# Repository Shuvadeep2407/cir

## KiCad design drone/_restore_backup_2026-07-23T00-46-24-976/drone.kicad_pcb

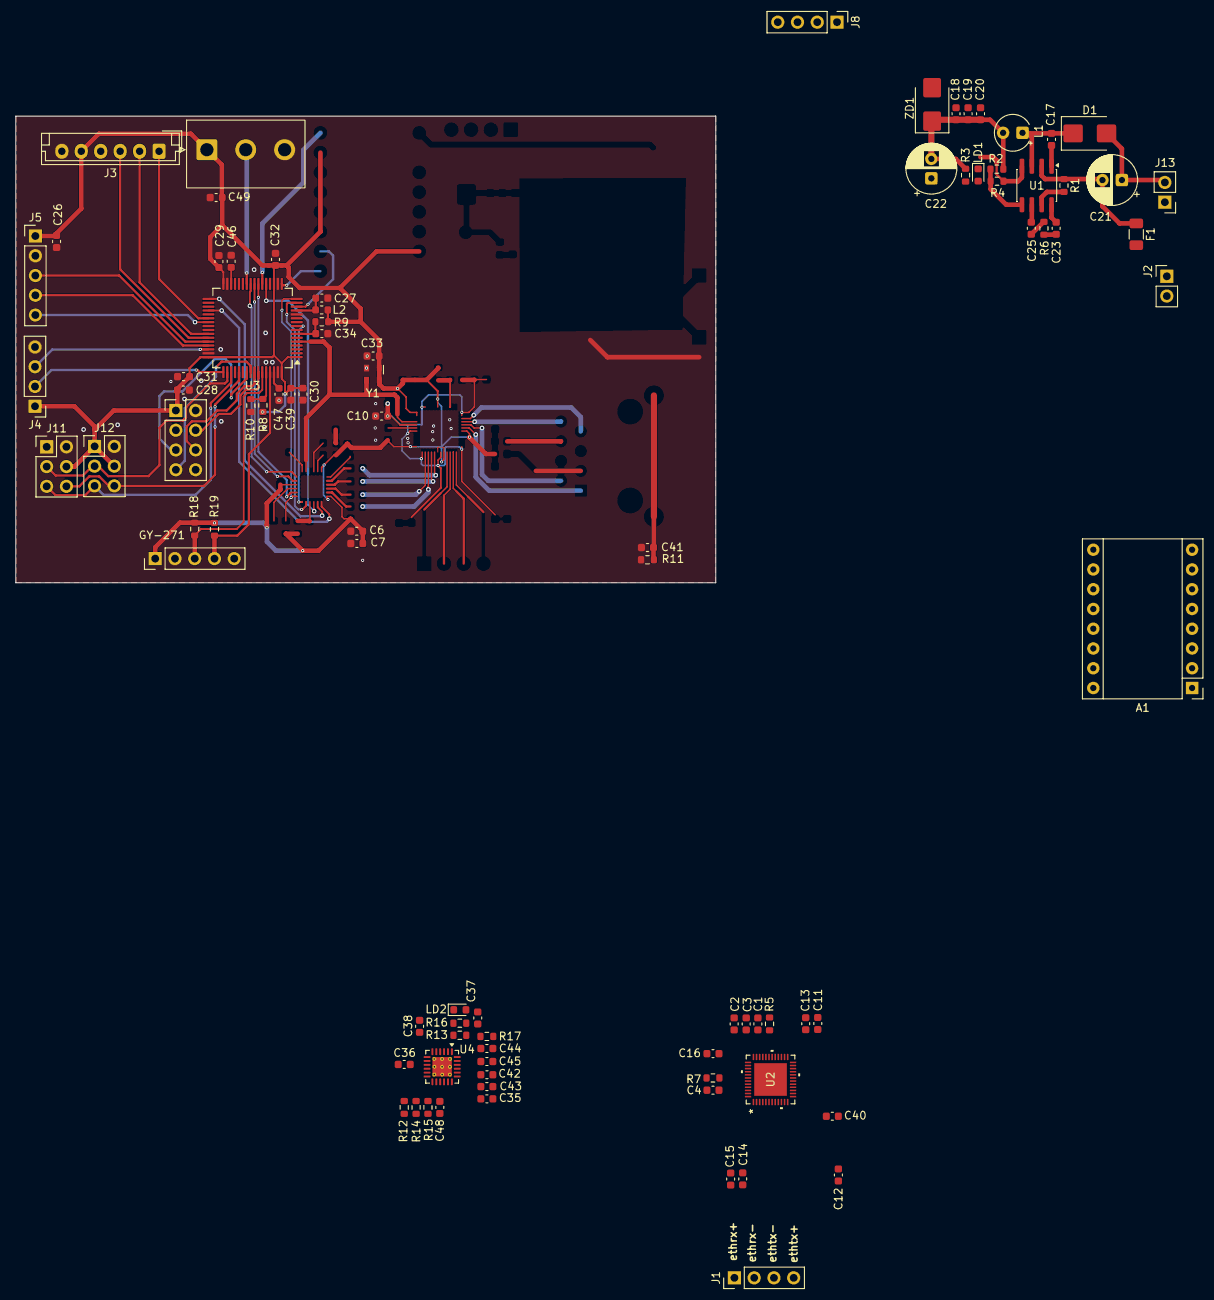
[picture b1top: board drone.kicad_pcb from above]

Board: 2 copper layers, 90.0 x 60.0 mm, 89 parts (0 on the bottom side), 75 nets.

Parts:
A1: A4988; Pololu_Breakout-16_15.2x20.3mm
C1, C2, C3, C4, C6, C7, C10, C11, C12, C13, C14, C15, C16, C17, C20, C23, C25, C26, C27, C28, C29, C30, C31, C32, C33, C34, C35, C36, C37, C38, C39, C40, C42, C43, C44, C45, C46, C47, C48, C49: 100nF; C_0603_1608Metric
C18: 10p; C_0603_1608Metric
C19: 33p; C_0603_1608Metric
C21, C22: 100uF D8.0mm_P3.50mm; CP_Radial_D6.3mm_P2.50mm
C41: 1nF; C_0603_1608Metric
D1: ss24; D_SMB
F1: 6w LIMIT; Fuse_1206_3216Metric
J1: cam eth; PinHeader_1x04_P2.54mm_Vertical
J2, J13: P_cam; PinHeader_1x02_P2.54mm_Vertical
J3: LRF; JST_EH_B6B-EH-A_1x06_P2.50mm_Vertical
J4: SWD; PinHeader_1x04_P2.54mm_Vertical
J5: gsm; PinHeader_1x05_P2.54mm_Vertical
J7: GY-271; PinHeader_1x05_P2.54mm_Vertical
J8: stapper; PinHeader_1x04_P2.54mm_Vertical
J9: C1101; PinHeader_2x04_P2.54mm_Vertical
J10: LIGHT; JST_NV_B03P-NV_1x03_P5.00mm_Vertical
J11, J12: INMP441; PinHeader_2x03_P2.54mm_Vertical
L1: 10µH; CP_Radial_Tantal_D4.5mm_P2.50mm
L2: 36nH; L_0603_1608Metric
LD1, LD2: LED; LED_0603_1608Metric
R1, R4, R5, R9, R10, R12, R13, R15, R18, R19: 10K; R_0603_1608Metric
R2: 26.1K; R_0603_1608Metric
R3, R16: 1K; R_0603_1608Metric
R6: 4k7; R_0603_1608Metric
R7: 2.49kΩ (1% tolerance); R_0603_1608Metric
R8: 100K; R_0603_1608Metric
R11: 1M; R_0603_1608Metric
R14: 4.7K; R_0603_1608Metric
R17: 12.1K; R_0603_1608Metric
U1: EUP3484A; SOIC-8_3.9x4.9mm_P1.27mm
U2: RTL8305NB-CG; QFN48_RTL8305_RTK
U3: STM32H563RGTx; LQFP-64_10x10mm_P0.5mm
U4: LAN8720A; VQFN-24-1EP_4x4mm_P0.5mm_EP2.5x2.5mm_ThermalVias
Y1: ASDMB-25MHz; Oscillator_SMD_Abracon_ASDMB-4Pin_2.5x2.0mm
ZD1: 3v3; D_SMB

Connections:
+3V3: A1.2 (VDD), A1.10 (MS1), A1.11 (MS2), A1.12 (MS3), A1.13 (~RESET), A1.14 (~SLEEP), C1.1, C2.1, C3.1, C4.1, C6.1, C7.1, C18.1, C19.1, C20.1, C22.2, C26.1, C28.1, C29.1, C30.1, C31.1, C32.1, C33.1, C35.1, C36.1, C37.1, C39.1, C40.1, C49.1, J3.5, J4.1, J5.1, J7.1, J9.1, J10.1, J11.4, J12.1, J12.4, L1.2, L2.1, R2.1, R3.1, R5.2, R8.2, R9.2, R13.1, R14.2, R15.2, R18.2, R19.2, U2.6 (AVDDH), U2.8 (AVDDH), U2.18 (AVDDH), U2.31 (DVDDH), U2.37 (V331N), U2.38 (AVDDHPLL), U2.48 (AVDDH), U3.1 (VBAT), U3.19 (VDD), U3.32 (VDD), U3.48 (VDD), U3.64 (VDD), U4.1 (VDD2A), U4.9 (VDDIO), U4.19 (VDD1A), Y1.1 (Standby), Y1.4 (VDD), ZD1.1 (K)
+12V: A1.8 (VMOT), C21.2, F1.1, J13.1, R1.1, U1.2 (IN)
/25MHz: U2.40 (XI), U3.5 (PH0), U4.5 (XTAL1/CLKIN), Y1.3 (Out)
/C1101 _clk: J9.5, U3.55 (PB3(JTDO)
/C1101 _cs: J9.4, U3.58 (PB6)
/C1101 _mosi: J9.6, U3.57 (PB5)
/C1101_miso: J9.7, U3.56 (PB4(NJTRST))
/CRS_DV: U3.23 (PA7), U4.11 (CRS_DV/MODE2)
/DIR: A1.16 (DIR), U3.17 (PA3)
/ENABLE: A1.9 (~ENABLE), U3.22 (PA6)
/LIGHT_EN: J10.2, U3.26 (PB0)
/LRF_EN: J3.1, U3.38 (PC7)
/LRF_RX: J3.2, U3.42 (PA9)
/LRF_TX: J3.3, U3.43 (PA10)
/MDC: U3.9 (PC1), U4.13 (MDC)
/MDIO: R14.1, U3.16 (PA2), U4.12 (MDIO)
/PPS: J5.5, U3.39 (PC8)
/REF_CLK: U3.15 (PA1), U4.14 (~INT/REFCLKO)
/RXD0: U3.24 (PC4), U4.8 (RXD0/MODE0)
/RXD1: U3.25 (PC5), U4.7 (RXD1/MODE1)
/STEP: A1.15 (STEP), U3.14 (PA0)
/SWCLK: J4.2, U3.49 (PA14(JTCK)
/SWDIO: J4.3, U3.46 (PA13(JTMS)
/TXD0: U3.33 (PB12), U4.17 (TXD0)
/TXD1: U3.36 (PB15), U4.18 (TXD1)
/TX_EN: U3.21 (PA5), U4.16 (TXEN)
/eth_mcu_rx+: C42.1, U2.2 (RXIPI)
/eth_mcu_rx-: C43.1, U2.3 (RXINI)
/eth_mcu_tx+: C44.1, U2.5 (TXOPI)
/eth_mcu_tx-: C45.1, U2.4 (TXONI)
/ethrx+: J1.1, U2.9 (TXOP2)
/ethrx-: J1.2, U2.10 (TXON2)
/ethtx+: J1.4, U2.12 (RXIP2)
/ethtx-: J1.3, U2.11 (RXIN2)
/fb: R2.2, R4.1, U1.5 (FB)
/gsm_rx: J5.4, U3.45 (PA12)
/gsm_tx: J5.3, U3.44 (PA11)
/sck: J11.5, J12.5, U3.51 (PC10)
/scl: J7.4, R19.1, U3.61 (PB8)
/sd: J11.6, J12.6, U3.53 (PC12)
/sda: J7.3, R18.1, U3.59 (PB7)
/staper1: A1.3 (1B), J8.1
/staper2: A1.4 (1A), J8.2
/staper3: A1.5 (2A), J8.3
/staper4: A1.6 (2B), J8.4
/sw: C17.1, D1.1 (K), L1.1, U1.3 (SW)
/ws: J11.3, J12.3, U3.50 (PA15(JTDI))
GND: A1.1 (GND), A1.7 (GND), C1.2, C2.2, C3.2, C4.2, C6.2, C7.2, C10.2, C11.2, C12.2, C13.2, C14.2, C15.2, C16.2, C18.2, C19.2, C20.2, C21.1, C22.1, C23.2, C26.2, C27.2, C28.2, C29.2, C30.2, C31.2, C32.2, C33.2, C34.2, C35.2, C36.2, C37.2, C38.2, C39.2, C40.2, C41.2, C46.2, C47.2, C48.2, C49.2, D1.2 (A), J2.2, J3.6, J4.4, J5.2, J7.2, J9.2, J10.3, J11.1, J11.2, J12.2, J13.2, LD1.1 (K), LD2.1 (K), R4.2, R6.2, R7.1, R10.1, R11.2, R12.1, R17.1, U1.4 (GND), U2.49 (EPAD), U3.12 (VSSA), U3.18 (VSS), U3.31 (VSS), U3.47 (VSS), U3.63 (VSS), U4.25 (VSS), Y1.2 (GND), ZD1.2 (A)
unnamed: C25.2, R6.1
unnamed: C41.1, R11.1
unnamed: C46.1, U3.30 (VCAP)
unnamed: C47.1, U3.62 (VCAP)
unnamed: F1.2, J2.1
unnamed: LD1.2 (A), R3.2
unnamed: LD2.2 (A), R16.2
unnamed: C17.2, U1.1 (BS)
unnamed: C25.1, U1.6 (COMP)
unnamed: R1.2, U1.7 (EN)
unnamed: C23.1, U1.8 (SS)
unnamed: C10.1, C11.1, C12.1, C13.1, C14.1, C15.1, C16.1, U2.1 (AVDDL), U2.7 (DVDDL), U2.13 (AVDDL), U2.23 (AVDDL), U2.24 (DVDDL), U2.35 (DVDDL), U2.36 (V10OUT), U2.41 (AVDDLPLL), U2.43 (AVDDL)
unnamed: R7.2, U2.42 (IBREF)
unnamed: R5.1, U2.27 (RESETB)
unnamed: R8.1, R10.2, U3.60 (BOOT0)
unnamed: C34.1, R9.1, U3.7 (NRST)
unnamed: C27.1, L2.2, U3.13 (VDDA)
unnamed: R16.1, U4.3 (LED1/REGOFF)
unnamed: R13.2, U4.2 (LED2/~INTSEL)
unnamed: R17.2, U4.24 (RBIAS)
unnamed: R12.2, U4.10 (RXER/PHYAD0)
unnamed: C45.2, U4.22 (RXN)
unnamed: C44.2, U4.23 (RXP)
unnamed: C43.2, U4.20 (TXN)
unnamed: C42.2, U4.21 (TXP)
unnamed: C38.1, U4.6 (VDDCR)
unnamed: C48.1, R15.1, U4.15 (~RST)

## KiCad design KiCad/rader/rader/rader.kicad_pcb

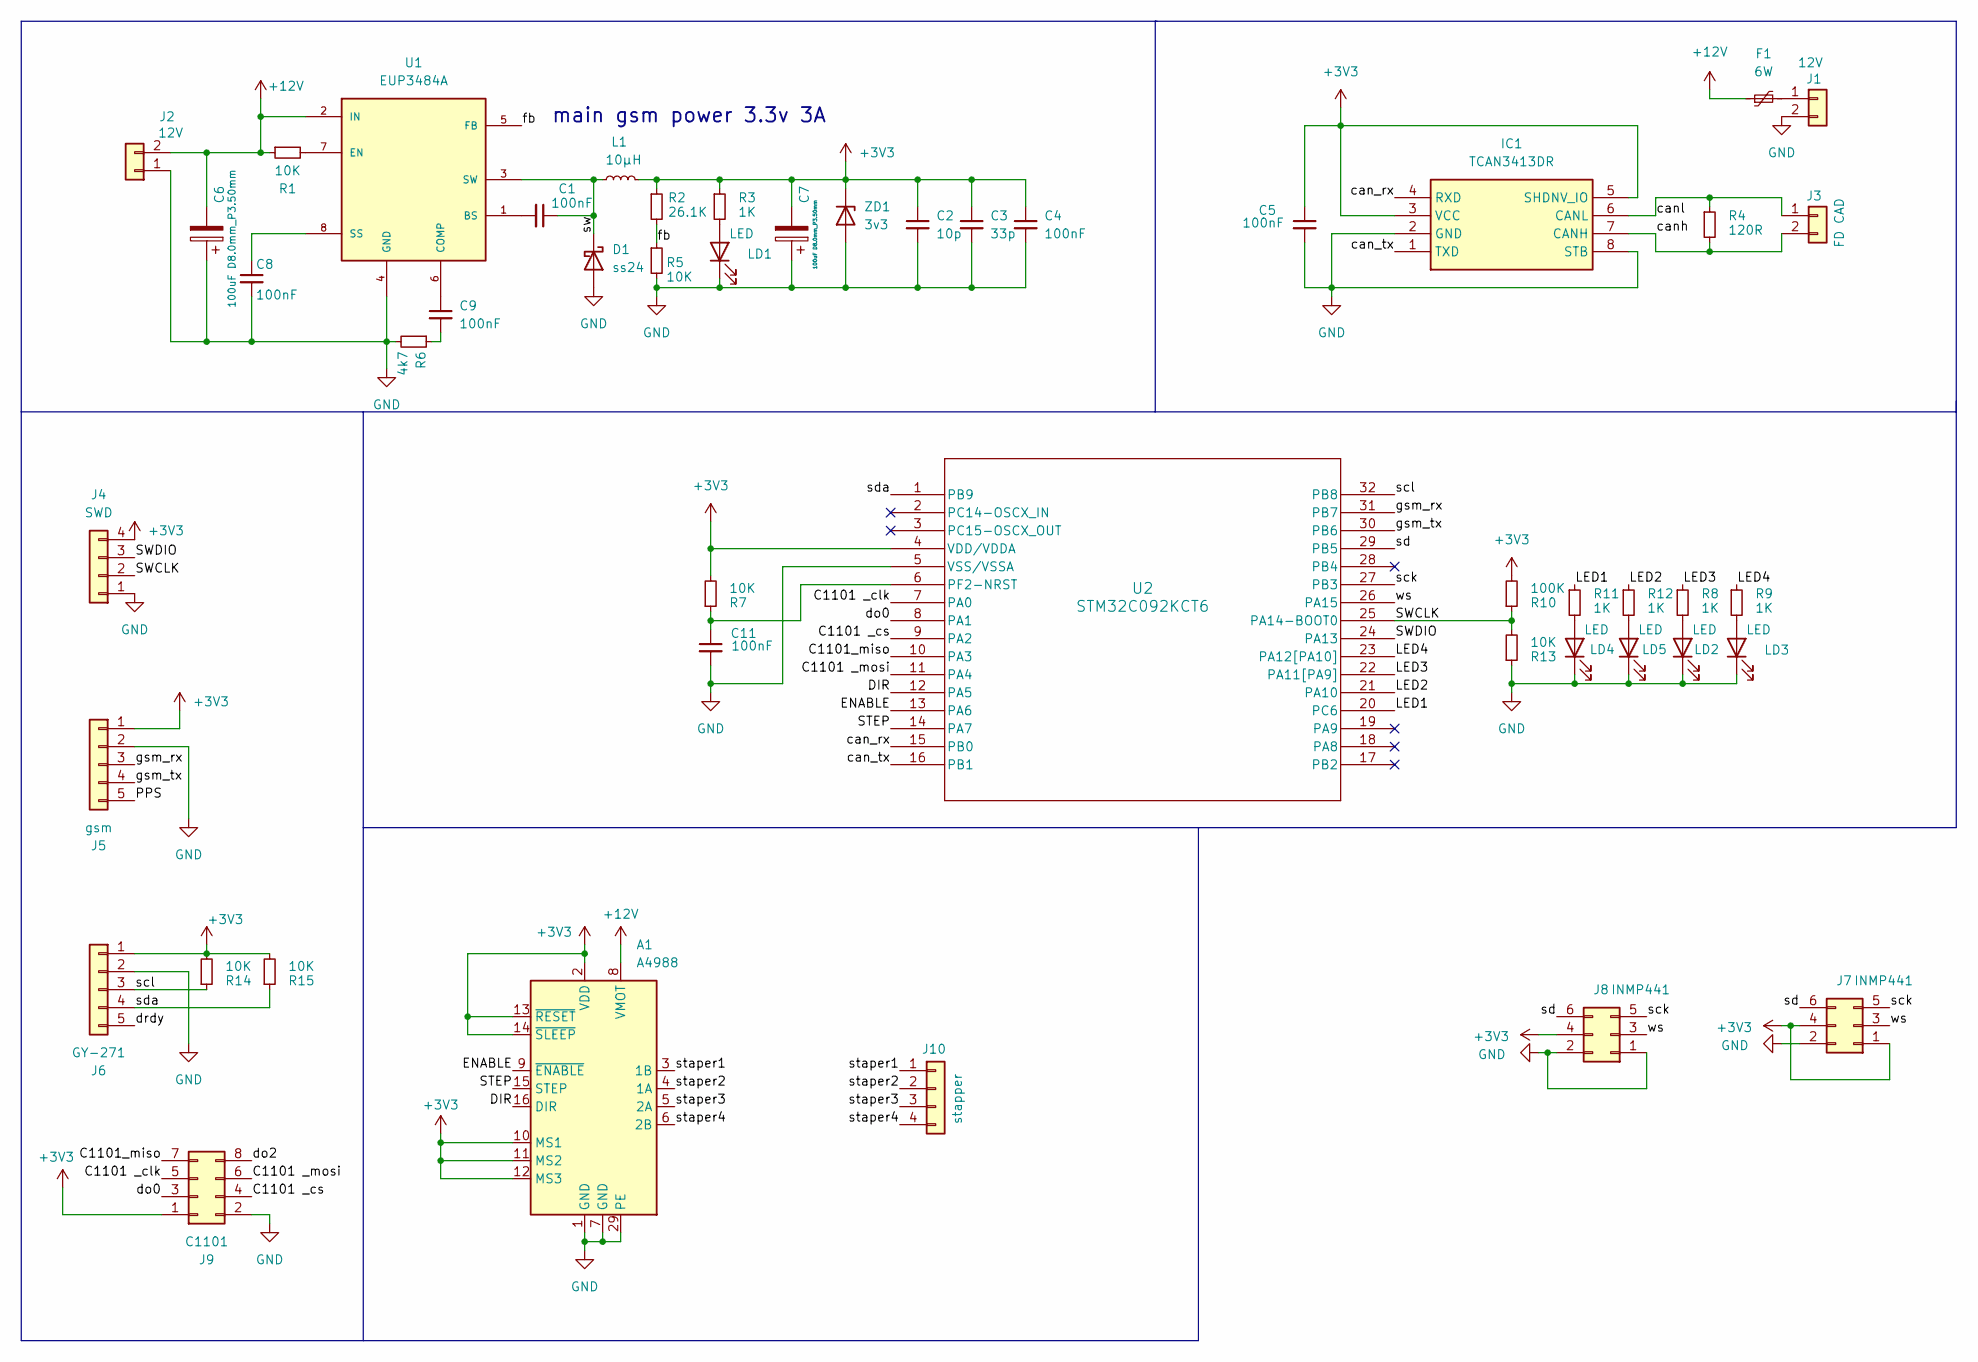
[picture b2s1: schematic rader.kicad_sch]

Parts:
A1: A4988; Pololu_Breakout-16_15.2x20.3mm
C1, C4, C5, C8, C9, C11: 100nF; C_0603_1608Metric
C2: 10p; C_0603_1608Metric
C3: 33p; C_0603_1608Metric
C6, C7: 100uF D8.0mm_P3.50mm; CP_Radial_D6.3mm_P2.50mm
D1: ss24; D_SMB
F1: 6W; Fuse_1206_3216Metric
IC1: TCAN3413DR; SOIC127P600X175-8N; Manufacturer_Part_Number TCAN3413DR; Mouser Part Number 595-TCAN3413DR
J1, J2: 12V; PinHeader_1x02_P2.54mm_Vertical
J3: FD CAD; PinHeader_1x02_P2.54mm_Vertical
J4: SWD; PinHeader_1x04_P2.54mm_Vertical
J5: gsm; PinHeader_1x05_P2.54mm_Vertical
J6: GY-271; PinHeader_1x05_P2.54mm_Vertical
J7, J8: INMP441; PinHeader_2x03_P2.54mm_Vertical
J9: C1101; PinHeader_2x04_P2.54mm_Vertical
J10: stapper; PinHeader_1x04_P2.54mm_Vertical
L1: 10µH; CP_Radial_Tantal_D4.5mm_P2.50mm
LD1, LD2, LD3, LD4, LD5: LED; LED_0603_1608Metric
R1, R5, R7, R13, R14, R15: 10K; R_0603_1608Metric
R2: 26.1K; R_0603_1608Metric
R3, R8, R9, R11, R12: 1K; R_0603_1608Metric
R4: 120R; R_0603_1608Metric
R6: 4k7; R_0603_1608Metric
R10: 100K; R_0603_1608Metric
U1: EUP3484A; SOIC-8_3.9x4.9mm_P1.27mm
U2: STM32C092KCT6; LQFP-32_7x7mm_P0.8mm
ZD1: 3v3; D_SMB

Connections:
+3V3: A1.2 (VDD), A1.10 (MS1), A1.11 (MS2), A1.12 (MS3), A1.13 (~RESET), A1.14 (~SLEEP), C2.1, C3.1, C4.1, C5.1, C7.2, IC1.3 (VCC), IC1.5 (SHDNV_IO), J4.4, J5.1, J6.1, J7.1, J7.4, J8.4, J9.1, L1.2, R2.1, R3.1, R7.2, R10.2, R14.2, R15.2, U2.4 (VDD/VDDA), ZD1.1 (K)
+12V: A1.8 (VMOT), C6.2, F1.1, J2.2, R1.1, U1.2 (IN)
/C1101 _clk: J9.5, U2.7 (PA0)
/C1101 _cs: J9.4, U2.9 (PA2)
/C1101 _mosi: J9.6, U2.11 (PA4)
/C1101_miso: J9.7, U2.10 (PA3)
/DIR: A1.16 (DIR), U2.12 (PA5)
/ENABLE: A1.9 (~ENABLE), U2.13 (PA6)
/LED1: R11.1, U2.20 (PC6)
/LED2: R12.1, U2.21 (PA10)
/LED3: R8.1, U2.22 (PA11[PA9])
/LED4: R9.1, U2.23 (PA12[PA10])
/PPS: J5.5
/STEP: A1.15 (STEP), U2.14 (PA7)
/SWCLK: J4.2, R10.1, R13.2, U2.25 (PA14-BOOT0)
/SWDIO: J4.3, U2.24 (PA13)
/can_rx: IC1.4 (RXD), U2.15 (PB0)
/can_tx: IC1.1 (TXD), U2.16 (PB1)
/canh: IC1.7 (CANH), J3.2, R4.2
/canl: IC1.6 (CANL), J3.1, R4.1
/do0: J9.3, U2.8 (PA1)
/do2: J9.8
/drdy: J6.5
/fb: R2.2, R5.1, U1.5 (FB)
/gsm_rx: J5.3, U2.31 (PB7)
/gsm_tx: J5.4, U2.30 (PB6)
/sck: J7.5, J8.5, U2.27 (PB3)
/scl: J6.3, R14.1, U2.32 (PB8)
/sd: J7.6, J8.6, U2.29 (PB5)
/sda: J6.4, R15.1, U2.1 (PB9)
/staper1: A1.3 (1B), J10.1
/staper2: A1.4 (1A), J10.2
/staper3: A1.5 (2A), J10.3
/staper4: A1.6 (2B), J10.4
/sw: C1.1, D1.1 (K), L1.1, U1.3 (SW)
/ws: J7.3, J8.3, U2.26 (PA15)
GND: A1.1 (GND), A1.7 (GND), A1.29 (PE), C2.2, C3.2, C4.2, C5.2, C6.1, C7.1, C8.2, C11.2, D1.2 (A), IC1.2 (GND), IC1.8 (STB), J1.2, J2.1, J4.1, J5.2, J6.2, J7.2, J8.1, J8.2, J9.2, LD1.1 (K), LD2.1 (K), LD3.1 (K), LD4.1 (K), LD5.1 (K), R5.2, R6.2, R13.1, U1.4 (GND), U2.5 (VSS/VSSA), ZD1.2 (A)
unnamed: C9.2, R6.1
unnamed: F1.2, J1.1
unnamed: LD1.2 (A), R3.2
unnamed: LD2.2 (A), R8.2
unnamed: LD3.2 (A), R9.2
unnamed: LD4.2 (A), R11.2
unnamed: LD5.2 (A), R12.2
unnamed: C1.2, U1.1 (BS)
unnamed: C9.1, U1.6 (COMP)
unnamed: R1.2, U1.7 (EN)
unnamed: C8.1, U1.8 (SS)
unnamed: C11.1, R7.1, U2.6 (PF2-NRST)

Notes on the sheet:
main gsm power 3.3v 3A

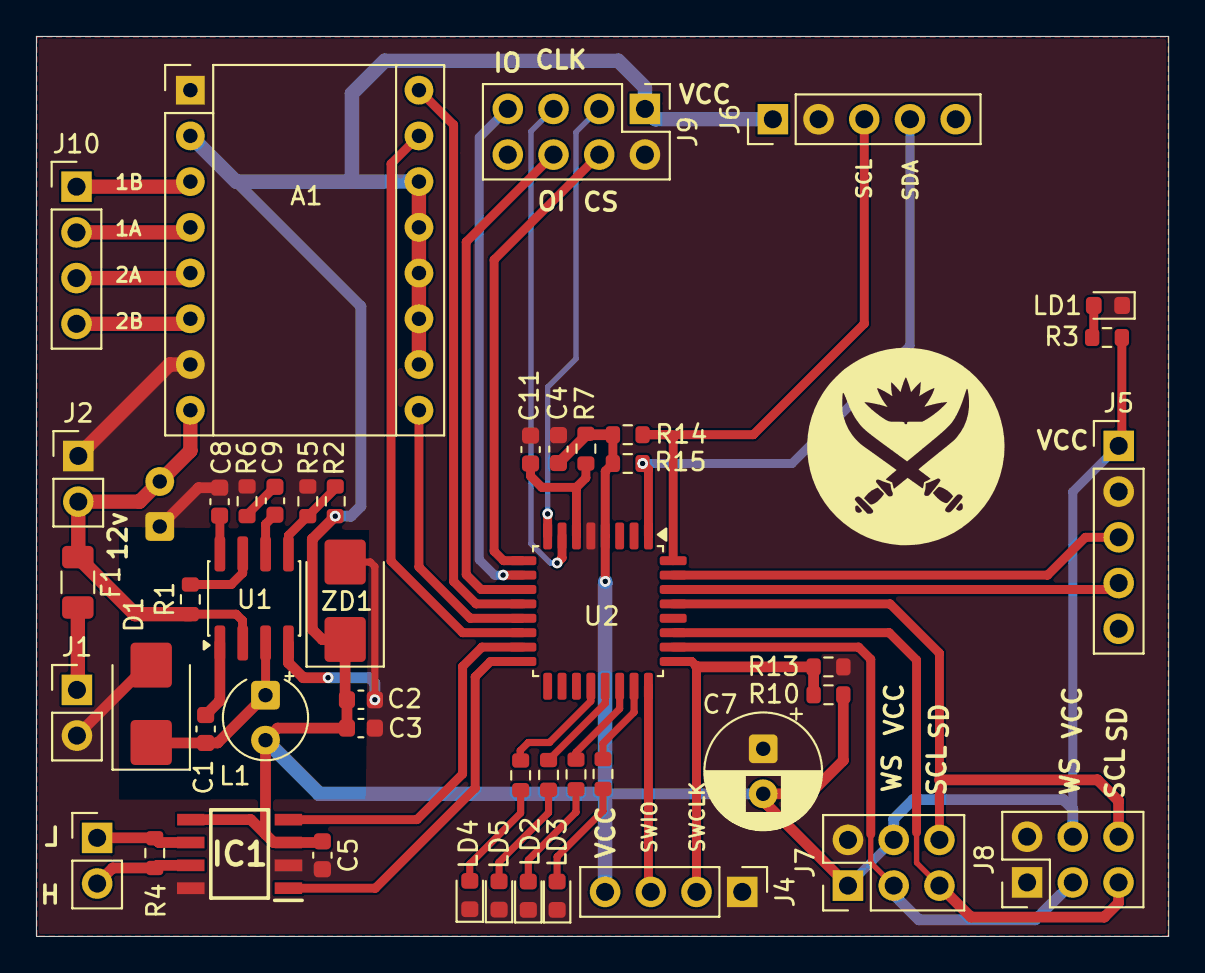
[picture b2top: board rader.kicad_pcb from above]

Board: 2 copper layers, 62.9 x 50.0 mm, 48 parts (1 on the bottom side), 46 nets.

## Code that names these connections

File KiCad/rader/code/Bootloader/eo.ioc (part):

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Mcu.Name=STM32C092KCTx
Mcu.Package=LQFP32
Mcu.UserName=STM32C092KCTx
PA0.GPIOParameters=GPIO_Label
PA0.GPIO_Label=C1101 _clk
PA0.Mode=Full_Duplex_Master
PA0.Signal=SPI2_SCK
PA1.GPIOParameters=GPIO_Label
PA1.GPIO_Label=DO0
PA1.Signal=GPIO_Output
PA10.GPIOParameters=GPIO_Label
PA10.GPIO_Label=LED2
PA10.Signal=GPIO_Output
PA11\ [PA9].GPIOParameters=GPIO_Label
PA11\ [PA9].GPIO_Label=LED3
PA11\ [PA9].Signal=GPIO_Output
PA12\ [PA10].GPIOParameters=GPIO_Label
PA12\ [PA10].GPIO_Label=LED4
PA12\ [PA10].Signal=GPIO_Output
PA13.Mode=Serial_Wire
PA13.Signal=DEBUG_SWDIO
PA14-BOOT0.Mode=Serial_Wire
PA14-BOOT0.Signal=DEBUG_SWCLK
PA15.GPIOParameters=GPIO_Label
PA15.GPIO_Label=ws
PA15.Mode=Half_Duplex_Master
PA15.Signal=I2S1_WS
PA2.GPIOParameters=GPIO_Label
PA2.GPIO_Label=c1101_clk
PA2.Signal=GPIO_Output
PA3.GPIOParameters=GPIO_Label
PA3.GPIO_Label=C1101_miso
PA3.Mode=Full_Duplex_Master
PA3.Signal=SPI2_MISO
PA4.GPIOParameters=GPIO_Label
PA4.GPIO_Label=C1101 _mosi
PA4.Mode=Full_Duplex_Master
PA4.Signal=SPI2_MOSI
PA5.GPIOParameters=GPIO_Label
PA5.GPIO_Label=DIR
PA5.Signal=GPIO_Output
PA6.GPIOParameters=GPIO_Label
PA6.GPIO_Label=ENABLE
PA6.Signal=GPIO_Output
PA7.GPIOParameters=GPIO_Label
PA7.GPIO_Label=STEP
PA7.Mode=PWM Generation1 CH1N
PA7.Signal=TIM1_CH1N
PB0.GPIOParameters=GPIO_Label
PB0.GPIO_Label=can_rx
PB0.Mode=FDCAN_Activate
PB0.Signal=FDCAN1_RX
PB1.GPIOParameters=GPIO_Label
PB1.GPIO_Label=can_tx
PB1.Mode=FDCAN_Activate
PB1.Signal=FDCAN1_TX
PB3.GPIOParameters=GPIO_Label
PB3.GPIO_Label=sck
PB3.Mode=Half_Duplex_Master
PB3.Signal=I2S1_CK
PB5.GPIOParameters=GPIO_Label
PB5.GPIO_Label=sd
PB5.Mode=Half_Duplex_Master
PB5.Signal=I2S1_SD
PB6.GPIOParameters=GPIO_Label
PB6.GPIO_Label=gsm_tx
PB6.Mode=Asynchronous
PB6.Signal=USART1_TX
PB7.GPIOParameters=GPIO_Label
PB7.GPIO_Label=gsm_rx
PB7.Mode=Asynchronous
PB7.Signal=USART1_RX
PB8.GPIOParameters=GPIO_Label
PB8.GPIO_Label=scl
PB8.Mode=I2C
PB8.Signal=I2C1_SCL
PB9.GPIOParameters=GPIO_Label
PB9.GPIO_Label=sda
PB9.Mode=I2C
PB9.Signal=I2C1_SDA
PC6.GPIOParameters=GPIO_Label
PC6.GPIO_Label=LED1
PC6.Signal=GPIO_Output
RCC.HSE_VALUE=8000000
RCC.SYSCLKFreq_VALUE=48000000
board=custom

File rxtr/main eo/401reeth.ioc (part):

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Mcu.Name=STM32F401R(D-E)Tx
Mcu.Package=LQFP64
Mcu.UserName=STM32F401RETx
PA10.Mode=Asynchronous
PA10.Signal=USART1_RX
PA11.Mode=Host_Only
PA11.Signal=USB_OTG_FS_DM
PA12.Mode=Host_Only
PA12.Signal=USB_OTG_FS_DP
PA13.GPIOParameters=GPIO_Label
PA13.GPIO_Label=TMS
PA13.Mode=Serial_Wire
PA13.Signal=SYS_JTMS-SWDIO
PA14.GPIOParameters=GPIO_Label
PA14.GPIO_Label=TCK
PA14.Mode=Serial_Wire
PA14.Signal=SYS_JTCK-SWCLK
PA2.GPIOParameters=GPIO_Speed,GPIO_PuPd,GPIO_Label,GPIO_Mode
PA2.GPIO_Label=USART_TX
PA2.GPIO_Mode=GPIO_MODE_AF_PP
PA2.GPIO_PuPd=GPIO_NOPULL
PA2.GPIO_Speed=GPIO_SPEED_FREQ_LOW
PA2.Mode=Asynchronous
PA2.Signal=USART2_TX
PA3.GPIOParameters=GPIO_Speed,GPIO_PuPd,GPIO_Label,GPIO_Mode
PA3.GPIO_Label=USART_RX
PA3.GPIO_Mode=GPIO_MODE_AF_PP
PA3.GPIO_PuPd=GPIO_NOPULL
PA3.GPIO_Speed=GPIO_SPEED_FREQ_LOW
PA3.Mode=Asynchronous
PA3.Signal=USART2_RX
PA5.Mode=Full_Duplex_Master
PA5.Signal=SPI1_SCK
PA6.Mode=Full_Duplex_Master
PA6.Signal=SPI1_MISO
PA7.Mode=Full_Duplex_Master
PA7.Signal=SPI1_MOSI
PA8.GPIOParameters=GPIO_Label
PA8.GPIO_Label=w5500_cs
PA8.Signal=GPIO_Output
PA9.Mode=Asynchronous
PA9.Signal=USART1_TX
PB0.GPIOParameters=GPIO_Label
PB0.GPIO_Label=a2
PB0.Signal=GPIO_Output
PB1.GPIOParameters=GPIO_Label
PB1.GPIO_Label=b2
PB1.Signal=GPIO_Output
PB10.Mode=Half_Duplex_Master
PB10.Signal=I2S2_CK
PB12.Mode=Half_Duplex_Master
PB12.Signal=I2S2_WS
PB15.Mode=Half_Duplex_Master
PB15.Signal=I2S2_SD
PB6.GPIOParameters=GPIO_Label
PB6.GPIO_Label=c1101_cs
PB6.Signal=GPIO_Output
PB8.Mode=I2C
PB8.Signal=I2C1_SCL
PB9.Mode=I2C
PB9.Signal=I2C1_SDA
PC10.Mode=Full_Duplex_Master
PC10.Signal=SPI3_SCK
PC11.Mode=Full_Duplex_Master
PC11.Signal=SPI3_MISO
PC12.Mode=Full_Duplex_Master
PC12.Signal=SPI3_MOSI
PC14-OSC32_IN.Mode=LSE-External-Oscillator
PC14-OSC32_IN.Signal=RCC_OSC32_IN
PC15-OSC32_OUT.Mode=LSE-External-Oscillator
PC15-OSC32_OUT.Signal=RCC_OSC32_OUT
PC4.GPIOParameters=GPIO_Label
PC4.GPIO_Label=a1
PC4.Signal=GPIO_Output
PC5.GPIOParameters=GPIO_Label
PC5.GPIO_Label=b1
PC5.Signal=GPIO_Output
PC6.Mode=Asynchronous
PC6.Signal=USART6_TX
PC7.Mode=Asynchronous
PC7.Signal=USART6_RX
RCC.HSE_VALUE=8000000
RCC.SYSCLKFreq_VALUE=84000000
RCC.SYSCLKSource=RCC_SYSCLKSOURCE_PLLCLK
board=NUCLEO-F401RE
boardIOC=true
